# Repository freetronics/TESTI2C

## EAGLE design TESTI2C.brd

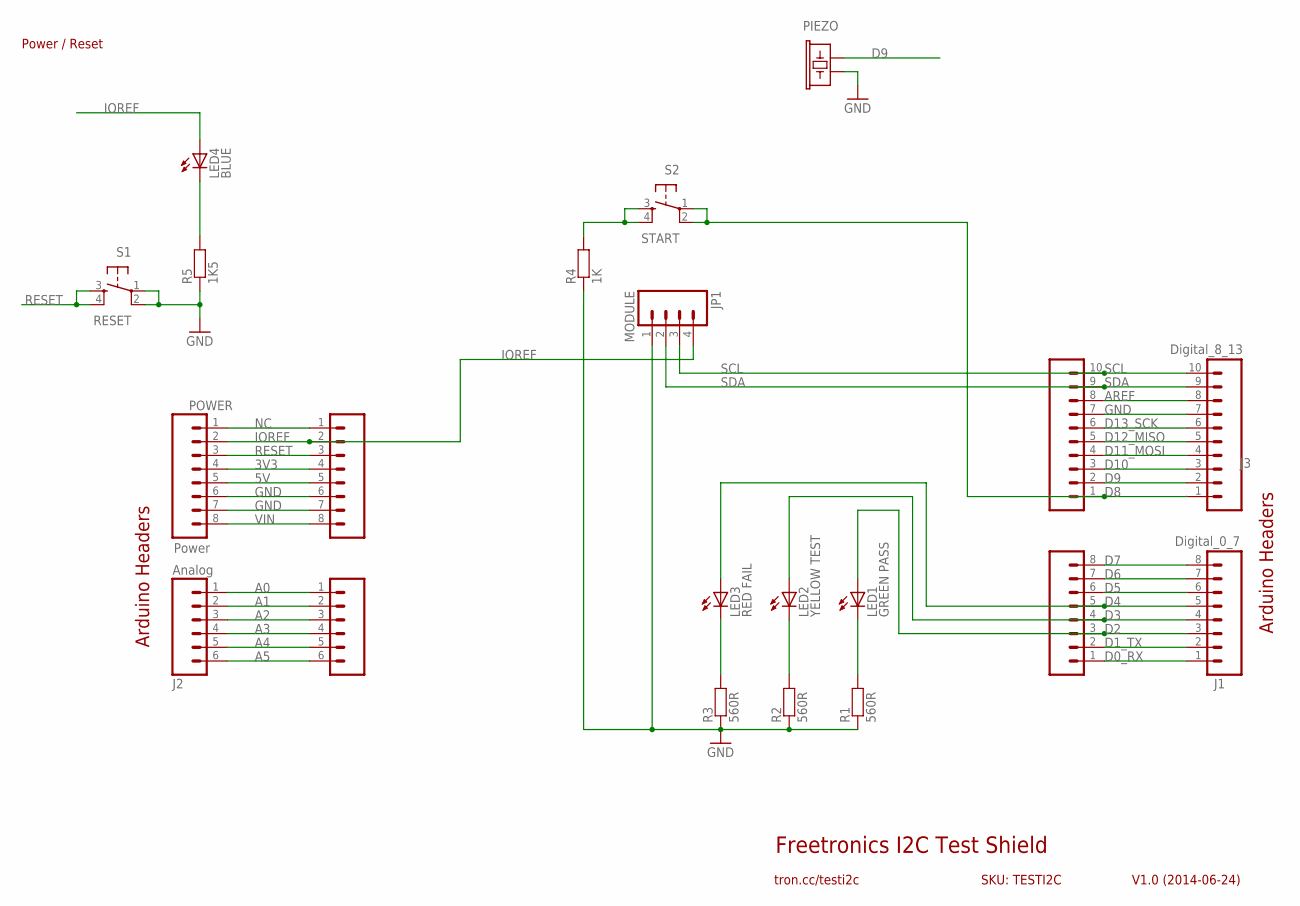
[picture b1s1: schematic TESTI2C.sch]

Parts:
J1: Digital_0_7; 1X08
J2: Analog; 1X06
J3: Digital_8_13; 1X10
JP1: MODULE; 1X04
LED1: GREEN PASS; LED-0603
LED2: YELLOW TEST; LED-0603
LED3: RED FAIL; LED-0603
LED4: BLUE; LED-0603
PIEZO: BUZZERSMD12X12; BUZZER-12X12-SMT
POWER: Power; 1X08
R1, R2, R3: 560R; 0603
R4: 1K; 0603
R5: 1K5; 0603
S1: RESET; TACTILE-PTH
S2: START; TACTILE-PTH
SL1: Digital_0_7; 1X08
SL2: Analog; 1X06
SL3: Digital_8_13; 1X10
SLP: Power; 1X08

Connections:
3V3: POWER.4, SLP.4
5V: POWER.5, SLP.5
A0: J2.1, SL2.1
A1: J2.2, SL2.2
A2: J2.3, SL2.3
A3: J2.4, SL2.4
A4: J2.5, SL2.5
A5: J2.6, SL2.6
AREF: J3.8, SL3.8
D0_RX: J1.1, SL1.1
D1_TX: J1.2, SL1.2
D2: J1.3, LED1.A, SL1.3
D3: J1.4, LED2.A, SL1.4
D4: J1.5, LED3.A, SL1.5
D5: J1.6, SL1.6
D6: J1.7, SL1.7
D7: J1.8, SL1.8
D8: J3.1, S2.1, S2.2, SL3.1
D9: J3.2, PIEZO.2, SL3.2
D10: J3.3, SL3.3
D11_MOSI: J3.4, SL3.4
D12_MISO: J3.5, SL3.5
D13_SCK: J3.6, SL3.6
GND: J3.7, JP1.1, PIEZO.1, POWER.6, POWER.7, R1.1, R2.1, R3.1, R4.1, R5.1, S1.1, S1.2, SL3.7, SLP.6, SLP.7
IOREF: JP1.4, LED4.A, POWER.2, SLP.2
unnamed: LED1.C, R1.2
unnamed: LED2.C, R2.2
unnamed: LED3.C, R3.2
unnamed: LED4.C, R5.2
unnamed: R4.2, S2.3, S2.4
NC: POWER.1, SLP.1
RESET: POWER.3, S1.3, S1.4, SLP.3
SCL: J3.10, JP1.3, SL3.10
SDA: J3.9, JP1.2, SL3.9
VIN: POWER.8, SLP.8

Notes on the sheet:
Freetronics I2C Test Shield
V1.0 (2014-06-24)
tron.cc/testi2c
SKU: TESTI2C
Arduino Headers
Power / Reset

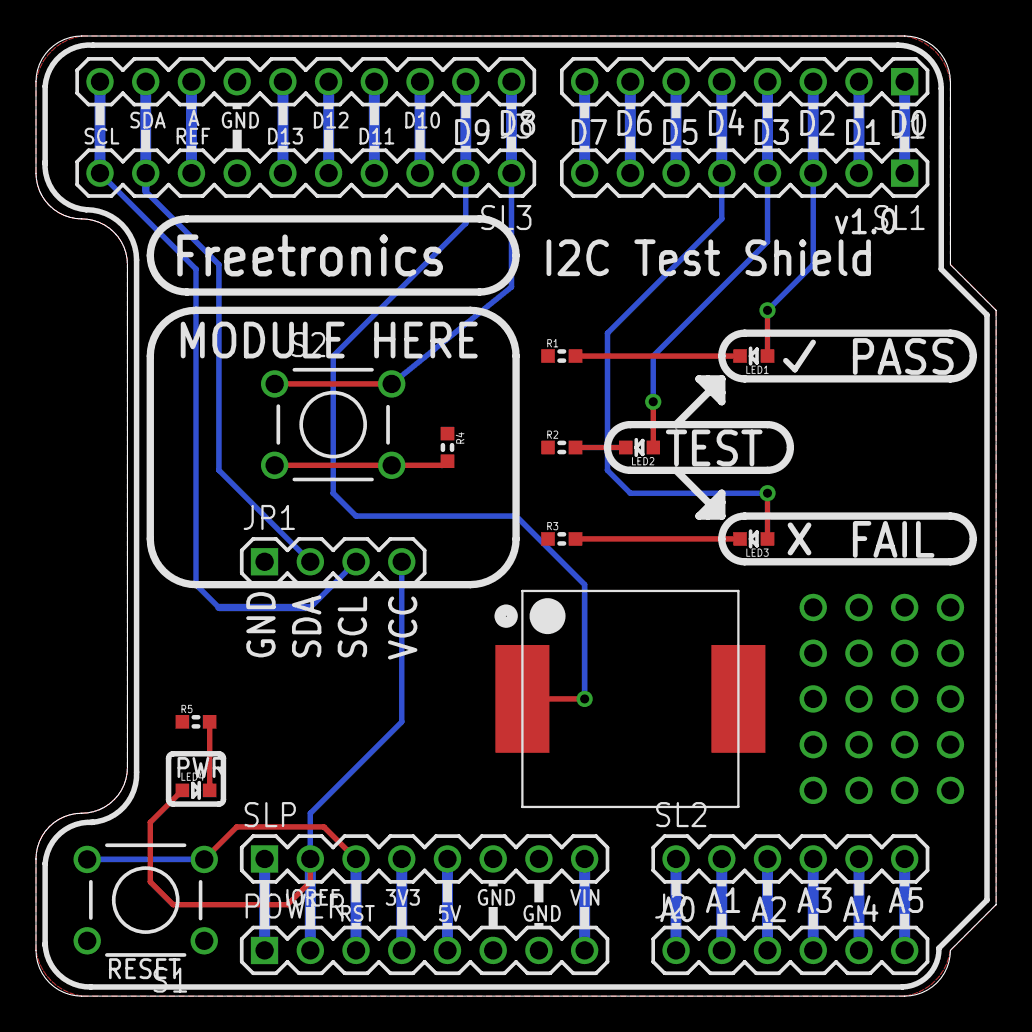
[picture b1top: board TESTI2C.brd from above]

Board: 2 copper layers, 53.3 x 53.3 mm, 21 parts (0 on the bottom side), 35 nets.

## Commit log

2014-06-27 Initial project import
2014-06-27 Added piezo
2019-04-24 Routing and silkscreen for v1.0 release

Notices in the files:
TESTI2C.brd:
(c) 2014 Freetronics Pty Ltd
